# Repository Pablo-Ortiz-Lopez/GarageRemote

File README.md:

# Multi-Door Garage Remote

Welcome to the Multi-Door Garage Remote repository! This project aims to provide a versatile solution for remotely controlling multiple garage doors that operate on the 433MHz fixed code protocol. While the current implementation is based on the fixed code protocol, it has the potential to be extended to support rolling code protocols and other RF parameters. Additionally, it has the necessary hardware to open garage doors operating at 280MHz, although this feature is yet to be implemented and tested.

## Features

1. **Multi-Door Support**: Control multiple garage doors using a single remote device.
2. **433MHz Protocol**: Designed to work with garage doors utilizing the 433MHz fixed code protocol.
3. **Potential for Expansion**: The architecture is built to potentially accommodate rolling code protocols and other RF parameters in the future.
4. **Low Power Consumption**: The board features a battery charging module and uses a Li-Po battery. It has been optimized to consume only 2 µA during inactivity.

## Contents

This repository contains:

1. **Electronics Design**: Detailed electronic schematics and PCB layouts to help you build the remote device.
2. **Firmware**: The firmware code that runs on the microcontroller, allowing it to communicate with garage doors.
3. **3D Printed Case Design** (Pending): The design files for the 3D printed case that will house the remote device.
4. **Documentation**: Additional information can be found on my blog posts:
   1. [Basics of Radio Communications](https://ortizma.com/p/reading-rf-signals/)

## Getting Started

To get started with this project, follow these steps:

1. **Electronics Assembly**: Review the electronics design and assemble the required components according to the schematics provided.
2. **Generate and Replace Codes**: Before flashing the firmware, generate the appropriate codes for your garage doors using the provided Node-JS script, and replace the provided ones. The firmware currently has codes for 3 garages with 2 doors each, which have been slightly altered for security reasons.
3. **Firmware Installation**: Use ICSP to flash the firmware into the Atmega328P microcontroller.
4. **Testing and Configuration**: Test the remote with your garage doors. Use SDR to troubleshoot any mismatches between the generated signal and the one generated by your remote.
5. **3D Printed Case** (Pending): Once available, 3D print the case and assemble the remote device within it.

## Coming soon
In the future, I plan to include:
* A 3D Printed case.
* Support for doors that operate at frequencies as low as 280MHz.
## Contributions

Contributions to this project are welcome! If you have ideas for improvements, bug fixes, or extensions to support different protocols, feel free to open an issue or submit a pull request.

## Disclaimer

Please note that this project involves working with RF protocols and electronics. Incorrect handling or usage can lead to unintended consequences or safety hazards. Be sure to understand what you're doing and follow best practices when assembling and using the remote device.

## Contact

For more information, updates, and detailed documentation, visit [ortizma.com](https://ortizma.com). Feel free to reach out to the project maintainer via email at pabloortiz132@gmail.com.

I hope you find this project useful and inspiring! Happy tinkering!

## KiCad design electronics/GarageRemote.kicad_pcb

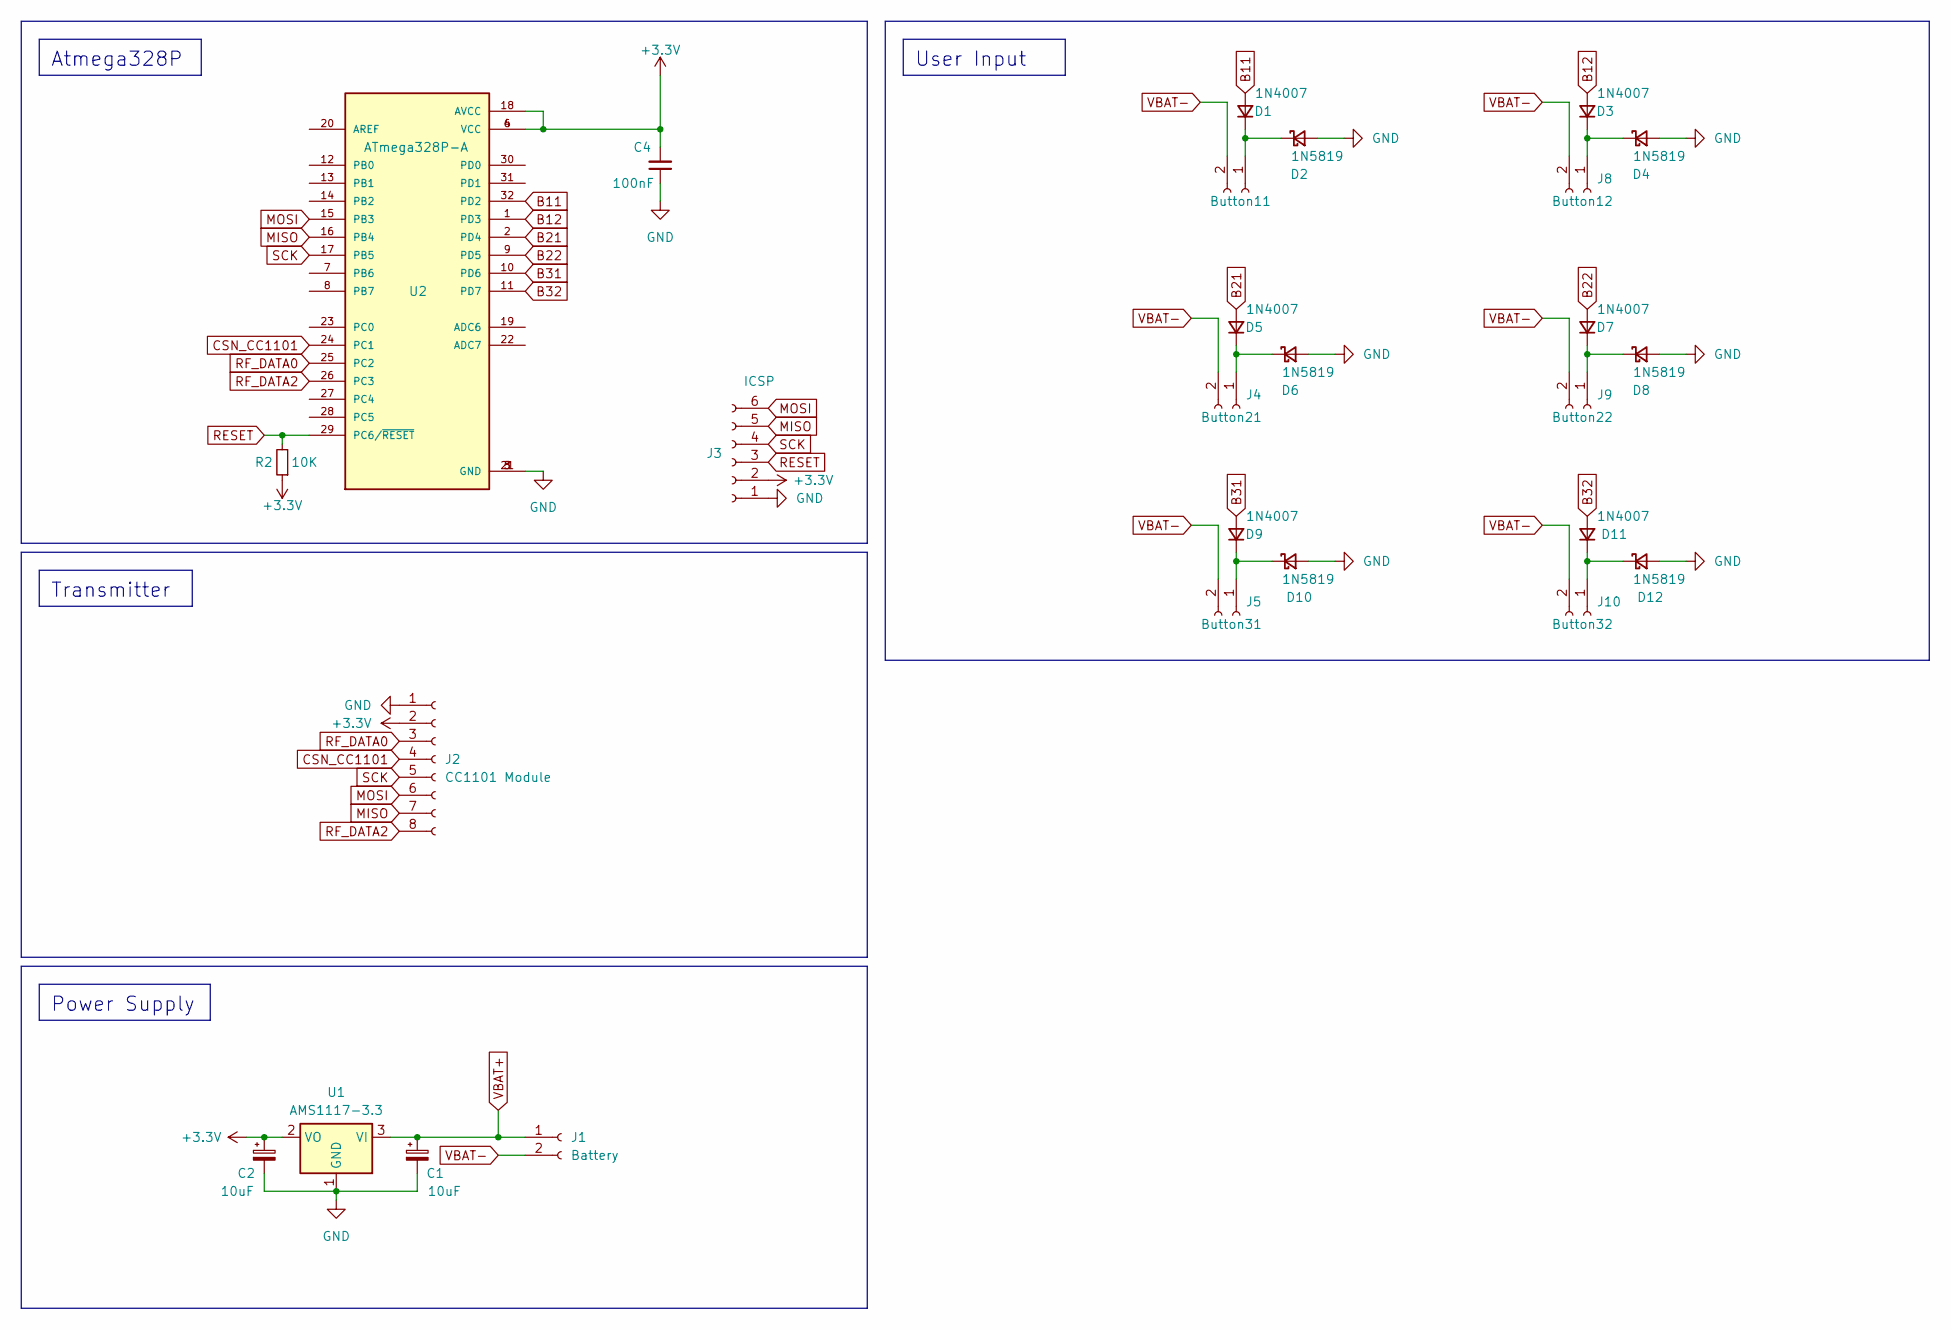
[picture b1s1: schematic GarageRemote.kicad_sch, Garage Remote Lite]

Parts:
C1, C2: 10uF; CP_Elec_5x5.9
C4: 100nF; C_1210_3225Metric_Pad1.33x2.70mm_HandSolder
D1, D3, D5, D7, D9, D11: 1N4007; D_SOD-523
D2, D4, D6, D8, D10, D12: 1N5819; D_SOD-523
J1: Battery; BS-2032-3
J2: CC1101 Module; PE07-M1101D-SMA
J3: ICSP; JST_PH_B6B-PH-K_1x06_P2.00mm_Vertical
J4: Button21; 4.5mm switch
J5: Button31; 4.5mm switch
J7: Button11; 4.5mm switch
J8: Button12; 4.5mm switch
J9: Button22; 4.5mm switch
J10: Button32; 4.5mm switch
R2: 10K; R_1206_3216Metric_Pad1.30x1.75mm_HandSolder
U1: AMS1117-3.3; SOT-223-3_TabPin2
U2: ATmega328P-A; Atmega328p-TQFP

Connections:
+3.3V: C2.1, C4.2, J2.2, J3.2, R2.1, U1.2 (VO), U2.4 (VCC), U2.6 (VCC), U2.18 (AVCC)
B11: D1.2 (A), U2.32 (PD2)
B12: D3.2 (A), U2.1 (PD3)
B21: D5.2 (A), U2.2 (PD4)
B22: D7.2 (A), U2.9 (PD5)
B31: D9.2 (A), U2.10 (PD6)
B32: D11.2 (A), U2.11 (PD7)
CSN_CC1101: J2.4, U2.24 (PC1)
GND: C1.2, C2.2, C4.1, D2.2 (A), D4.2 (A), D6.2 (A), D8.2 (A), D10.2 (A), D12.2 (A), J2.1, J3.1, U1.1 (GND), U2.3 (GND), U2.5 (GND), U2.21 (GND)
MISO: J2.7, J3.5, U2.16 (PB4)
MOSI: J2.6, J3.6, U2.15 (PB3)
unnamed: D1.1 (K), D2.1 (K), J7.1
unnamed: D3.1 (K), D4.1 (K), J8.1
unnamed: D5.1 (K), D6.1 (K), J4.1
unnamed: D7.1 (K), D8.1 (K), J9.1
unnamed: D9.1 (K), D10.1 (K), J5.1
unnamed: D11.1 (K), D12.1 (K), J10.1
RESET: J3.3, R2.2, U2.29 (PC6/~RESET)
RF_DATA0: J2.3, U2.25 (PC2)
RF_DATA2: J2.8, U2.26 (PC3)
SCK: J2.5, J3.4, U2.17 (PB5)
VBAT+: C1.1, J1.1, U1.3 (VI)
VBAT-: J1.2, J4.2, J5.2, J7.2, J8.2, J9.2, J10.2

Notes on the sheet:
User Input
Atmega328P
Power Supply
Transmitter

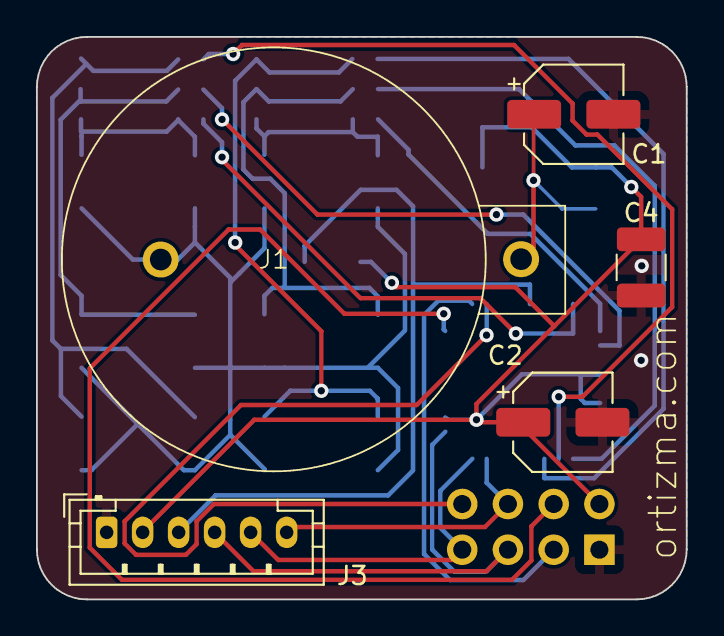
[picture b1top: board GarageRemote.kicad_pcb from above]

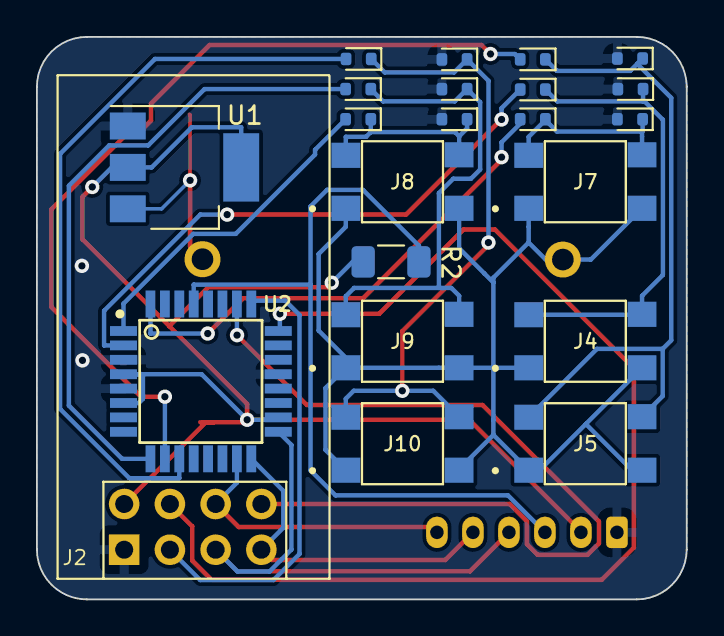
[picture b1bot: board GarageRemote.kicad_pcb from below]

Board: 2 copper layers, 36.1 x 31.2 mm, 27 parts (22 on the bottom side), 23 nets.

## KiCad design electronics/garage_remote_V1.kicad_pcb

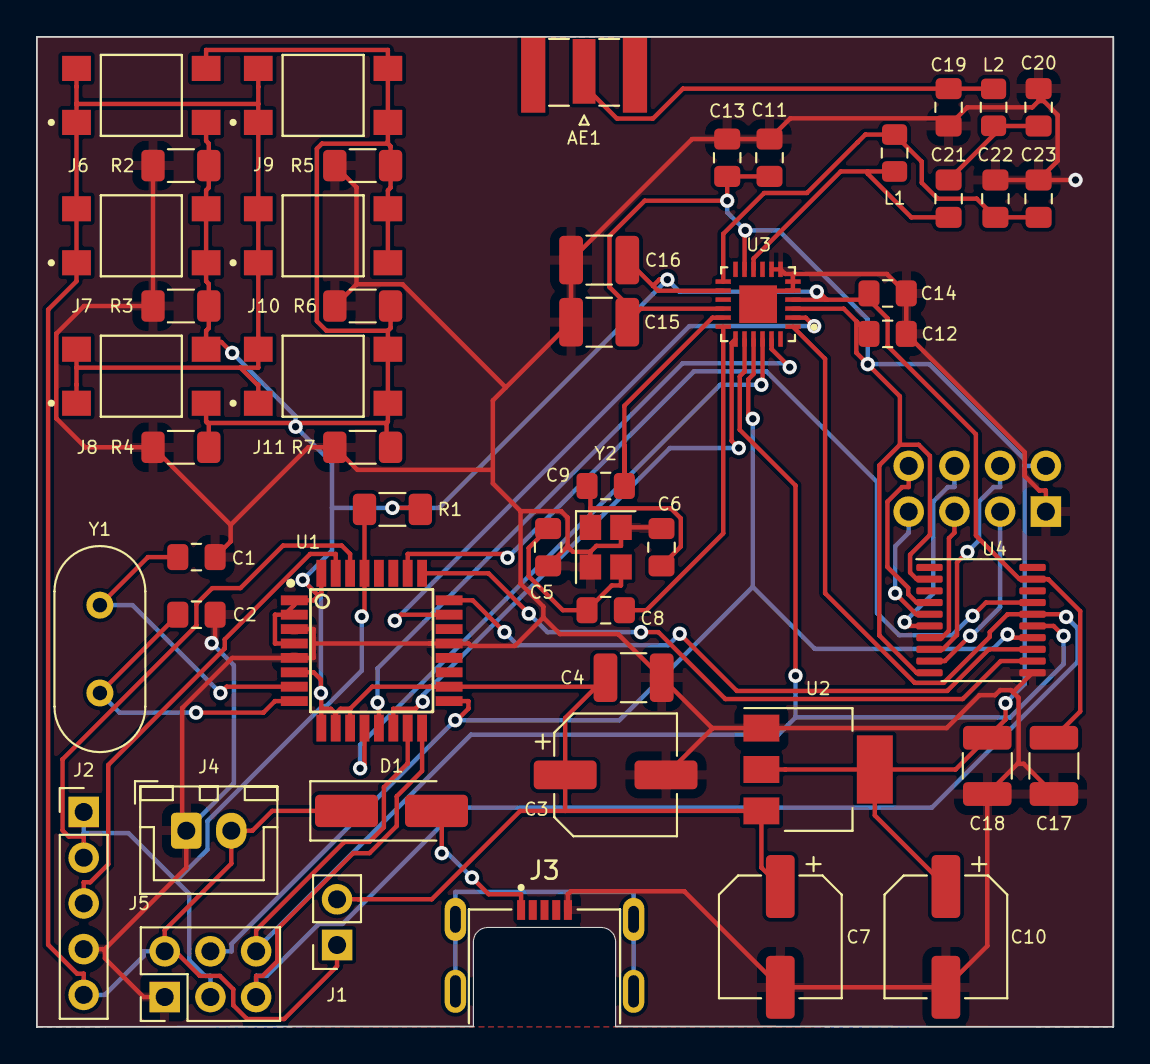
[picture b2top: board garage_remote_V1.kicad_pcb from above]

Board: 2 copper layers, 59.8 x 55.0 mm, 52 parts (1 on the bottom side), 35 nets.

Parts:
AE1: Antenna; SMA-J-P-X-ST-EM1_EdgeMount
C1, C2: 22pF; C_0805_2012Metric_Pad1.18x1.45mm_HandSolder
C3, C7, C10: 10uF; CP_Elec_6.3x4.9
C4, C15, C16, C17, C18: 100nF; C_1210_3225Metric_Pad1.33x2.70mm_HandSolder
C5, C6: 11pF; C_0805_2012Metric_Pad1.18x1.45mm_HandSolder
C8, C9: 1.5nF; C_0805_2012Metric_Pad1.18x1.45mm_HandSolder
C11: 220pF; C_0805_2012Metric_Pad1.18x1.45mm_HandSolder
C12, C13, C14: 10nF; C_0805_2012Metric_Pad1.18x1.45mm_HandSolder
C19, C20: 10pF; C_0805_2012Metric_Pad1.18x1.45mm_HandSolder
C21: 100pF; C_0805_2012Metric_Pad1.18x1.45mm_HandSolder
C22: 330pF; C_0805_2012Metric_Pad1.18x1.45mm_HandSolder
C23: 680pF; C_0805_2012Metric_Pad1.18x1.45mm_HandSolder
D1: 1N4001; D_SMA_Handsoldering
J1: Jumper; 2.54mm Jumper
J2: SERIAL; PinHeader_1x05_P2.54mm_Vertical
J3: 47642-0001; MOLEX_47642-0001
J4: Battery; JST_XH_B2B-XH-A_1x02_P2.50mm_Vertical
J5: ICSP; PinHeader_2x03_P2.54mm_Vertical
J6: Button11; 4.5mm switch
J7: Button21; 4.5mm switch
J8: Button31; 4.5mm switch
J9: Button12; 4.5mm switch
J10: Button22; 4.5mm switch
J11: Button32; 4.5mm switch
J12: CC1101 Module; PE07-M1101D-SMA
L1: 51nH; L_0805_2012Metric_Pad1.15x1.40mm_HandSolder
L2: 22nH; L_0805_2012Metric_Pad1.15x1.40mm_HandSolder
R1, R2, R3, R4, R5, R6, R7: 10k; R_1206_3216Metric_Pad1.30x1.75mm_HandSolder
U1: ATmega328P-A; Atmega328p-TQFP
U2: AMS1117-3.3; SOT-223-3_TabPin2
U3: MAX7060ATGT; MAX7060-TQFN24
U4: TXS0108EPW; TSSOP-20_4.4x6.5mm_P0.65mm
Y1: 16MHz; Crystal_HC49-4H_Vertical
Y2: 14.318MHz; Crystal_SMD_Abracon_ABM8G-4Pin_3.2x2.5mm

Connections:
+3.3V: C10.1, C11.1, C12.1, C13.1, C15.1, C18.2, J12.2, U2.2 (VO), U3.3 (DVDD), U3.11 (PAVDD), U3.16 (AVDD), U4.2 (VCCA), U4.10 (OE)
+5V: C3.1, C4.2, C7.1, C14.1, C16.1, C17.2, J1.2, J6.2, J7.2, J8.2, J9.2, J10.2, J11.2, R1.2, R2.1, R3.1, R4.1, R5.1, R6.1, R7.1, U1.1 (PD3), U1.2 (PD4), U1.4 (VCC), U1.6 (VCC), U1.9 (PD5), U1.10 (PD6), U1.11 (PD7), U1.18 (AVCC), U1.32 (PD2), U2.3 (VI), U3.4 (GPOVDD), U3.14 (VDD5), U4.19 (VCCB)
/CSN_CC1101_3V3: J12.4, U4.8 (A7)
/MISO_3V3: J12.7, U4.5 (A4)
/MOSI_3V3: J12.6, U4.6 (A5)
/RF2_DATA0_3V3: J12.3, U4.9 (A8)
/RF2_DATA2_3V3: J12.8, U4.4 (A3)
/SCK_3V3: J12.5, U4.7 (A6)
CSN_7060: U1.14 (PB2), U3.19 (~CS_DEV)
CSN_CC1101: U1.24 (PC1), U4.13 (B7)
GND: C1.1, C2.1, C3.2, C4.1, C5.1, C6.1, C7.2, C10.2, C11.2, C12.2, C13.2, C14.2, C15.2, C16.2, C17.1, C18.1, C19.1, C20.1, C22.1, C23.1, J2.4, J3.5 (GND), J4.1, J5.1, J12.1, R2.2, R3.2, R4.2, R5.2, R6.2, R7.2, U1.3 (GND), U1.5 (GND), U1.21 (GND), U2.1 (GND), U3.5 (FREQ0), U3.6 (FREQ1), U3.7 (FREQ2), U3.8 (LSHDN), U3.25 (EPAD), U4.11 (GND), Y2.2, Y2.4
MISO: J5.5, U1.16 (PB4), U3.1 (GPO2_MOD), U4.16 (B4)
MOSI: J5.6, U1.15 (PB3), U3.20 (SDI_PWR1), U4.15 (B5)
unnamed: AE1.1 (A), C19.2, L2.1
unnamed: C5.2, C8.1, Y2.3
unnamed: C6.2, C9.1, Y2.1
unnamed: C20.2, C21.1, L2.2
unnamed: D1.2 (A), J3.1 (VBUS)
unnamed: J3.S1 (SHIELD), J3.S2 (SHIELD), J3.S3 (SHIELD), J3.S4 (SHIELD)
unnamed: C1.2, U1.7 (PB6), Y1.2
unnamed: C2.2, U1.8 (PB7), Y1.1
unnamed: C8.2, U3.18 (XTAL1)
unnamed: C9.2, U3.17 (XTAL2)
PAOUT: C21.2, L1.2, U3.10 (PAOUT)
PAVOUT: C22.2, C23.2, L1.1, U3.13 (PAVOUT)
RESET: J2.1, J5.3, R1.1, U1.29 (PC6/~RESET)
RF1_DATA: U1.13 (PB1), U3.23 (DIN)
RF1_DATA1: U1.23 (PC0), U3.2 (GPO1)
RF1_ENABLE: U1.12 (PB0), U3.22 (ENABLE)
RF2_DATA0: U1.25 (PC2), U4.12 (B8)
RF2_DATA2: U1.26 (PC3), U4.17 (B3)
RX: J2.2, U1.30 (PD0)
SCK: J5.4, U1.17 (PB5), U3.21 (SCLK_PWR0), U4.14 (B6)
TX: J2.3, U1.31 (PD1)
VCC: D1.1 (K), J1.1, J2.5, J4.2, J5.2, J6.1, J7.1, J8.1, J9.1, J10.1, J11.1

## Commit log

2023-08-18 Fix readme
2023-08-26 Improve readme & rename files
2023-09-02 disable frequency scanning since it has been proven unnecessary
2023-09-08 Modify driver to allow infinite packet length
2023-09-08 Migrate firmware to PlatformIO
2023-09-08 Simplify driver
2023-09-08 Lint code
2023-09-08 Add workspace to use with PlatformIO
2023-09-11 Implement second PCB iteration
2023-09-15 Enable input pullups
2023-09-21 Adapt code to old board
2023-09-21 Use USBasp
2023-09-21 Update schematic
2023-09-24 Fix ground plane
2023-09-27 Start testing the MAX7060 chip on the old board
2023-10-05 Check MAX7060 Status
2023-10-07 Figured out that i forgot about the ENABLE pin
2023-10-22 Simplify defines
2023-12-09 Fix & simplify schematic
2023-12-09 Finished 1.1.0 design
2023-12-21 Bring code improvements from beta branch
2023-12-21 Set oldboard to 1
2023-12-21 Increase PA. Add comment. Prevent SPI initialization without button pressed.
2023-12-22 Prevent SPI init if no button pressed
2023-12-22 OLDBOARD=0
2023-12-22 Simplify code
2023-12-22 Increase PA to 12
2023-12-23 Bring new firmware developments to 2.0.0 board
2023-12-23 Fix typo
2024-01-01 Update codeDelays to work with first codeset
2024-01-01 fix codeDelays
